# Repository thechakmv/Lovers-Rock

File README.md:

# Dual-Stage Overdrive & Distortion Guitar Pedal

I created analog guitar effects pedal with two independent, switchable gain stageto achieve classic Thrash metal rhythm and lead tones: a soft-clipping overdrive with a **mid-boost** (+6 dB at 800 Hz) and a hard-clipping distortion with a **mid-scoop** (−6 to −10 dB across 400–800 Hz). The Pedal features a single-knob volume control, and gain controls for each stage as well. Each stage has true-bypass switching, so the two can run independently or be cascaded for stacked high-gain lead tones.

## Highlights

- Designed and simulated in LTSpice
- Two-stage analog signal chain built around TL072 op-amps
- True-bypass per stage via 3PDT footswitches, both stages can be activated simultaneously for cascaded gain
- Gyrator filter network for scooped voicings on distortion
- Single 9 V DC supply, ~15 mA total current draw
- PCB layout in KiCad with attention to signal integrity, and inter-stage isolation

## Signal Flow

```
                                                         
 Guitar ─> Input ─┬─> OD Stage ──┬─> Distortion ───> Tone ──┬> Volume ─> Output ─> Amp
          Buffer  │   (soft clip,│   (hard clip + (LPF)     │
          (TL072) │   mid-boost) │   Twin-T scoop)          │
                  │              │                          │
                  ▼              ▼                          ▼
                SW1 3PDT        SW2 3PDT                    Always
                true bypass     true bypass                 on signal path
```

When both switches are engaged, the OD output feeds the distortion stage input, producing a mid boosted overdrive. Each stage can also run alone for classic rock overdrive or for chuggy thrash metal rhythm tones.

## Design Specifications

| Parameter | Value |
|---|---|
| Supply | 9 V DC, center-negative, ~30 mA |
| OD Specs | peak at ~800Hz |
| OD clipping | Soft, symmetric, ±0.6 V (1N4148 anti-parallel in feedback) |
| Distortion Specs | Notch at around 800Hz |
| Distortion clipping | Hard, symmetric, ±0.6 V (1N4148 to Vref) |

## Design Philosophy

Thrash metal dictates that you have wo pedals. One Distortion, and one overdrive. For my pedal I wanted to combine these two topologies into one pedal. This design uses two intentionally distinct gain stages whose characters complement each other when cascaded overdrive to distortion.

The **overdrive stage** is a Tube Screamer-derived non-inverting topology with silicon diodes inside the feedback loop. The feedback RC network forms a band-pass response: lows roll off below 720 Hz and highs roll off above ~6 kHz at maximum gain. Inside the band the gradual diode conduction produces soft clipping that preserves the dry signal underneath the saturation, giving the characteristic transparent overdrive sound.

The **distortion stage** uses an inverting topology with diodes clamping the op-amp output directly to the Vref node. This produces hard, square-wave clipping rich in odd harmonics. The clipped signal then feeds a dual gyrator bandpass filter with peaks at 150 Hz, and 3.3KHz, carving out the middle frequencies by boosting the low and high frquencies.

The two stages are independently switchable: OD alone for classic rock, distortion alone for chunky rhythm, and both stacked for full-spectrum lead tones.

## Repository Structure

```
├── ltspice/
│   ├── Draft2.asc         
├── kicad/
│   ├── Lovers Rock.kicad_pro             Project file
│   ├── Lovers Rock.kicad_sch             Schematic
│   ├── Lovers Rock.kicad_pcb             Board layout
│   └── gerbers/                    Fabrication output (zipped Gerbers + drill)
└── images/
    ├──        
```

## Tools

**Software:** LTSpice, KiCad 10

**Test equipment:** multimeter, soldering iron, electrical components (caps, resistors etc.)

## Build Process

1. **Simulate.** Run AC and transient analyses in LTSpice for each stage. Verify gain curves, clipping shape, and Vref stability under load. Use `.step` to sweep gain pot values and see the response variation across the control range.

2. **Prototype.** Build stage-by-stage with bench power. tune by ear — swap diodes (Si vs. LED vs. asymmetric), tweak the frequencies, and adjust the gain ranges.

3. **PCB.** Re-capture the validated schematic in KiCad, assign through-hole footprints, lay out the board with the external component sockets neat their enclosure mounts. Generate Gerbers and fabricate via JLCPCB.

**TBD:**

1. **Verify.** Measure assembled pedal's frequency response and FFT using spectrul analyzer to compare against simulation predictions.
2. Order the PCBS, and prepare for final assembly

## Design Issues Encountered (and Fixed)

Some that problems came up during simulation and breadboarding that are worth documenting:

**Ridiculous power supply noise.** The power supply was being unrully, and I added bypass capacitors to each power trace to help mitigate the noise I was experiencing.

**Vref instability under heavy distortion.** The hard-clipping diodes were pumping current pulses into the Vref node, dragging it from 4.5 V down toward 1 V during the clipping phase. I Fixed it by adding a 1 kΩ series resistor between the distortion op-amp's output and the diode pair, limiting peak diode current and preserving Vref node.

**High-frequency oscillation at high gain.** The TL072 stages were prone to oscillation when driving purely capacitive loads, so I fixed it by adding a 470 Ω series isolation resistor between each op-amp output and its capacitive load.

## Skills Demonstrated

- Analog circuit design with op-amps
- Frequency-response shaping via active gyrator filter networks
- Soft-clipping vs. hard-clipping topology selection and harmonic analysis
- Single-supply audio biasing: Vref generation, AC coupling, bypass strategy
- SPICE simulation: AC sweep, transient analysis, FFT, parametric stepping
- PCB layout for analog audio: ground topology, decoupling, inter-stage isolation

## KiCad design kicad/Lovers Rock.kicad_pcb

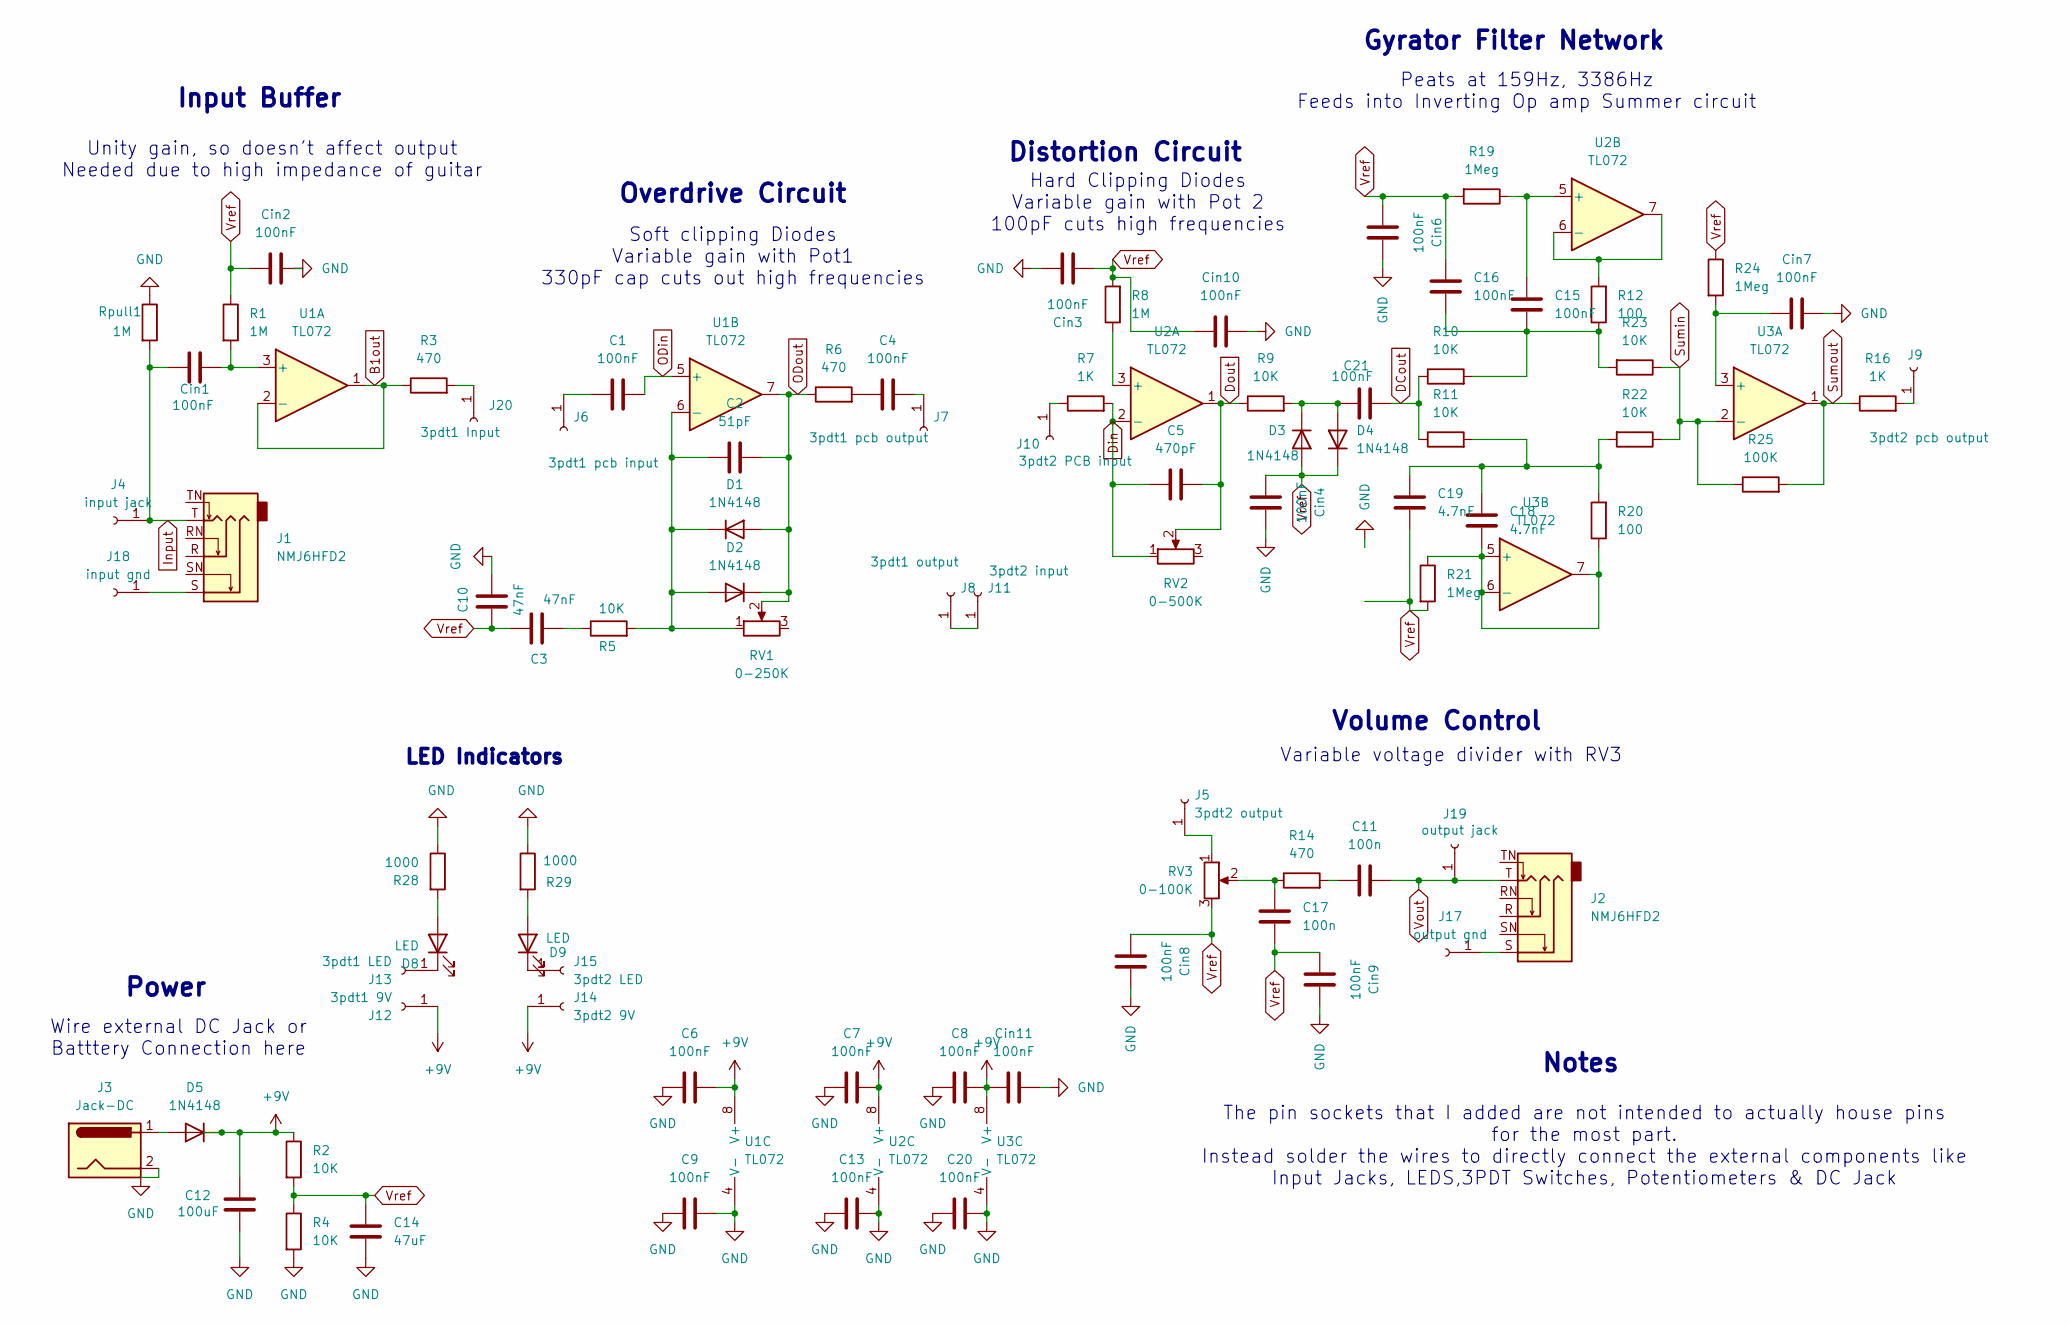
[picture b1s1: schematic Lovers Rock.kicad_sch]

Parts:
C1, C4, C6, C7, C8, C9, C13, C15, C16, C20, C21: 100nF; C_Disc_D5.0mm_W2.5mm_P5.00mm
C2: 51pF; C_Disc_D5.0mm_W2.5mm_P5.00mm
C3, C10: 47nF; C_Disc_D5.0mm_W2.5mm_P5.00mm
C5: 470pF; C_Disc_D5.0mm_W2.5mm_P5.00mm
C11, C17: 100n; C_Disc_D5.0mm_W2.5mm_P5.00mm
C12: 100uF; CP_Radial_D4.0mm_P1.50mm
C14: 47uF; CP_Radial_D4.0mm_P1.50mm
C18, C19: 4.7nF; C_Disc_D5.0mm_W2.5mm_P5.00mm
Cin1, Cin2, Cin3, Cin4, Cin6, Cin7, Cin8, Cin9, Cin10, Cin11: 100nF; C_Disc_D5.0mm_W2.5mm_P5.00mm
D1, D2, D3, D4, D5: 1N4148; D_DO-35_SOD27_P7.62mm_Horizontal
D8, D9: LED; PinSocket_1x02_P2.00mm_Vertical
J1, J2: NMJ6HFD2; Jack_6.35mm_Neutrik_NMJ6HFD2_Horizontal
J3: Jack-DC; PinSocket_1x02_P2.54mm_Vertical
J4: input jack; PinSocket_1x01_P2.00mm_Vertical
J5: 3pdt2 output; PinSocket_1x01_P2.00mm_Vertical
J6: 3pdt1 pcb input; PinSocket_1x01_P2.00mm_Vertical
J7: 3pdt1 pcb output; PinSocket_1x01_P2.00mm_Vertical
J8: 3pdt1 output; PinSocket_1x01_P2.00mm_Vertical
J9: 3pdt2 pcb output; PinSocket_1x01_P2.00mm_Vertical
J10: 3pdt2 PCB input; PinSocket_1x01_P2.00mm_Vertical
J11: 3pdt2 input; PinSocket_1x01_P2.00mm_Vertical
J12: 3pdt1 9V; PinSocket_1x01_P2.00mm_Vertical
J13: 3pdt1 LED; PinSocket_1x01_P2.00mm_Vertical
J14: 3pdt2 9V; PinSocket_1x01_P2.00mm_Vertical
J15: 3pdt2 LED; PinSocket_1x01_P2.00mm_Vertical
J17: output gnd; PinSocket_1x01_P2.00mm_Vertical
J18: input gnd; PinSocket_1x01_P2.00mm_Vertical
J19: output jack; PinSocket_1x01_P2.00mm_Vertical
J20: 3pdt1 Input; PinSocket_1x01_P2.00mm_Vertical
R1, R8: 1M; R_Axial_DIN0207_L6.3mm_D2.5mm_P7.62mm_Horizontal
R2, R4, R5, R9, R10, R11, R22, R23: 10K; R_Axial_DIN0207_L6.3mm_D2.5mm_P7.62mm_Horizontal
R3, R6, R14: 470; R_Axial_DIN0207_L6.3mm_D2.5mm_P7.62mm_Horizontal
R7, R16: 1K; R_Axial_DIN0207_L6.3mm_D2.5mm_P7.62mm_Horizontal
R12, R20: 100; R_Axial_DIN0207_L6.3mm_D2.5mm_P7.62mm_Horizontal
R19, R21, R24: 1Meg; R_Axial_DIN0207_L6.3mm_D2.5mm_P7.62mm_Horizontal
R25: 100K; R_Axial_DIN0207_L6.3mm_D2.5mm_P7.62mm_Horizontal
R28, R29: 1000; R_Axial_DIN0207_L6.3mm_D2.5mm_P7.62mm_Horizontal
RV1: 0-250K; PinSocket_1x02_P2.54mm_Vertical
RV2: 0-500K; PinSocket_1x02_P2.54mm_Vertical
RV3: 0-100K; PinSocket_1x03_P2.54mm_Vertical
Rpull1: 1M; R_Axial_DIN0207_L6.3mm_D2.5mm_P7.62mm_Horizontal
U1, U2, U3: TL072; DIP-8_W7.62mm_Socket

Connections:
+9V: C6.2, C7.2, C8.2, C12.1, Cin11.1, D5.1 (K), J12.1 (Pin_1_1), J14.1 (Pin_1_1), R2.1, U1.8 (V+), U2.8 (V+), U3.8 (V+)
B1out: R3.1, U1.1, U1.2 (-)
DCout: C21.1, R10.1, R11.1
Din: C5.1, R7.2, RV2.1, U2.2 (-)
Dout: C5.2, R9.1, RV2.2, U2.1
GND: C6.1, C7.1, C8.1, C9.1, C9.2, C10.2, C12.2, C13.1, C13.2, C14.2, C20.1, C20.2, Cin2.2, Cin3.2, Cin4.2, Cin6.2, Cin7.2, Cin8.2, Cin9.2, Cin10.2, Cin11.2, J3.2, R4.2, R28.1, R29.1, Rpull1.1, U1.4 (V-), U2.4 (V-), U3.4 (V-); also elsewhere on the board
Input: Cin1.1, J1.T, J4.1, Rpull1.2
unnamed: C3.2, R5.1
unnamed: C4.1, R6.2
unnamed: C11.2, R14.2
unnamed: C15.1, C16.1, R10.2, R12.1, R23.2
unnamed: C17.1, R14.1, RV3.2
unnamed: C18.2, C19.2, R11.2, R20.2, R22.2
unnamed: C2.1, D1.1 (K), D2.2 (A), R5.2, RV1.1, U1.6 (-)
unnamed: C21.2, D3.1 (K), D4.2 (A), R9.2
unnamed: D5.2 (A), J3.1
unnamed: D8.2 (A), R28.2
unnamed: D8.1 (K), J13.1 (Pin_1_1)
unnamed: D9.2 (A), R29.2
unnamed: D9.1 (K), J15.1 (Pin_1_1)
unnamed: J5.1 (Pin_1_1), RV3.1
unnamed: C1.1, J6.1 (Pin_1_1)
unnamed: C4.2, J7.1 (Pin_1_1)
unnamed: J9.1 (Pin_1_1), R16.2
unnamed: J10.1 (Pin_1_1), R7.1
unnamed: J8.1 (Pin_1_1), J11.1 (Pin_1_1)
unnamed: J2.S, J17.1 (Pin_1_1)
unnamed: J1.S, J18.1 (Pin_1_1)
unnamed: J20.1 (Pin_1_1), R3.2
unnamed: Cin1.2, R1.2, U1.3 (+)
unnamed: R8.1, U2.3 (+)
unnamed: C15.2, R19.1, U2.5 (+)
unnamed: R12.2, U2.6 (-), U2.7
unnamed: Cin7.1, R24.2, U3.3 (+)
unnamed: C18.1, R20.1, R21.1, U3.5 (+), U3.6 (-), U3.7
ODin: C1.2, U1.5 (+)
ODout: C2.2, D1.2 (A), D2.1 (K), R6.1, RV1.2, U1.7
Sumin: R22.1, R23.1, R25.1, U3.2 (-)
Sumout: R16.1, R25.2, U3.1
Vout: C11.1, J2.T, J19.1 (Pin_1_1)
Vref: C3.1, C10.1, C14.1, C16.2, C17.2, C19.1, Cin2.1, Cin3.1, Cin4.1, Cin6.1, Cin8.1, Cin9.1, Cin10.1, D3.2 (A), D4.1 (K), R1.1, R2.2, R4.1, R8.2, R19.2, R21.2, R24.1, RV3.3; also elsewhere on the board

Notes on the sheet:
Hard Clipping Diodes Variable gain with Pot 2 100pF cuts high frequencies
Peats at 159Hz, 3386Hz Feeds into Inverting Op amp Summer circuit
Unity gain, so doesn't affect output Needed due to high impedance of guitar
Variable voltage divider with RV3
LED Indicators
Notes
The pin sockets that I added are not intended to actually house pins for the most part. Instead solder the wires to directly connect the external components like Input Jacks, LEDS,3PDT Switches, Potentiometers & DC Jack
Wire external DC Jack or Batttery Connection here
Input Buffer
Soft clipping Diodes Variable gain with Pot1 330pF cap cuts out high frequencies
Overdrive Circuit
Volume Control
Power
Distortion Circuit
Gyrator Filter Network

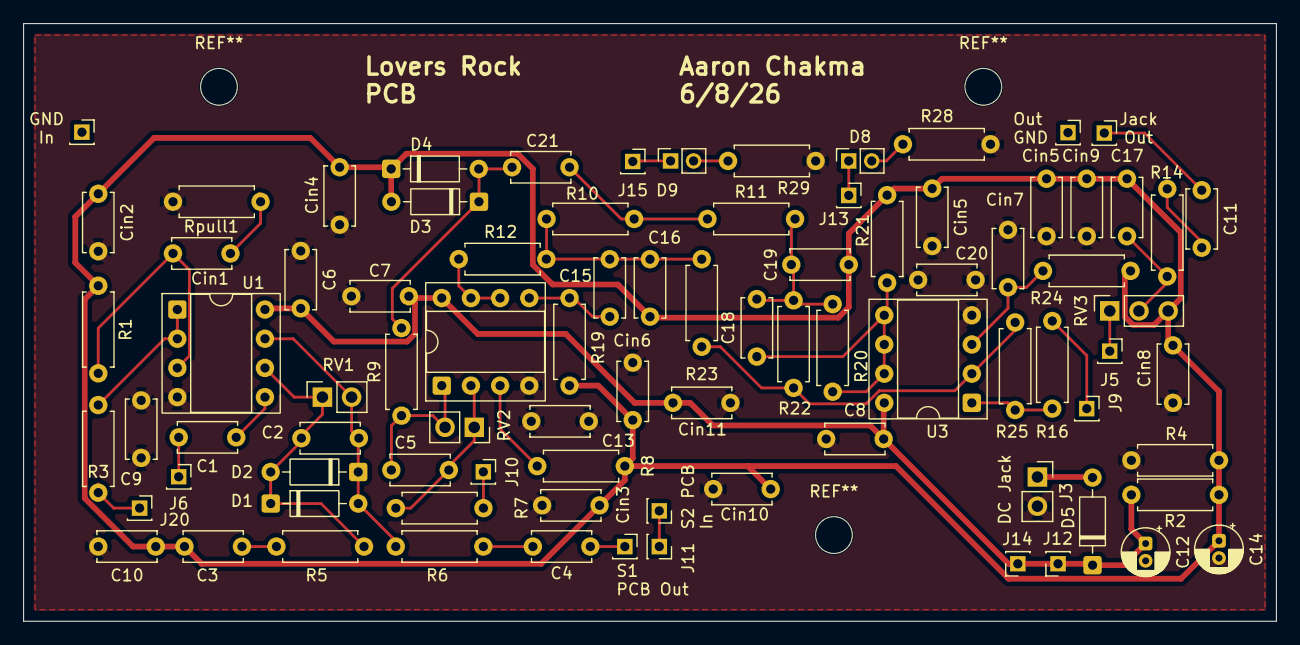
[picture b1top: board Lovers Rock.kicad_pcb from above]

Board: 2 copper layers, 109.0 x 52.0 mm, 86 parts (0 on the bottom side), 39 nets.

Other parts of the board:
Cin5, Cin5#2: 100nF; C_Disc_D5.0mm_W2.5mm_P5.00mm

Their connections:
GND: Cin5.2, Cin5#2.1; also elsewhere on the board
Vref: Cin5.1, Cin5#2.2; also elsewhere on the board

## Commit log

2026-06-08 Project complete
